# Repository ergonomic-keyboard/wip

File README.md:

# Custom Keyboard Generator

A browser-based tool for designing custom split ergonomic keyboards. Tap your finger positions, preview in 3D, and get a complete bill of materials with purchase links.

## Quick Start

Launch both the keyboard wizard and the requirement tracker:

```bash
cd /home/a/git/git/keyboard/wip
fuser -k 8080/tcp 8099/tcp 2>/dev/null; python3 -m http.server 8080 & node req-tracker.js & wait
```

- Keyboard wizard: http://localhost:8080/wizard.html
- Requirement tracker: http://localhost:8099

## Keyboard Wizard

Open http://localhost:8080/wizard.html and follow the 4 steps:

1. **Tap finger positions** — place your left hand flat and tap 3 key positions per finger column (pinky through thumb)
2. **3D preview** — interactive 3D model with shadows, wooden frame enclosure, click-to-press keys, exploded view, and component labels
3. **Bill of materials** — full parts list with prices and purchase links, download design files as a ZIP
4. **Firmware & test** — generated ZMK shield files, keymap visualization, native_posix hardware emulation tests

## Requirement Tracker

Tracks PASS/FAIL/SKIP status for each requirement in `final_requirements.md`, per git commit.

```bash
node req-tracker.js
```

Open http://localhost:8099.

**Features:**
- Each requirement from `final_requirements.md` is shown with its full text
- Mark each requirement PASS, FAIL, or SKIP
- Click the comment button to add notes (e.g. what's wrong, how to fix it)
- Edit requirement text inline (click the text, edit, click away to save)
- Add new requirements with the "+ Add requirement" button
- Navigate between git commits using the arrows in the top-right
- When navigating to a commit with no status, it inherits PASS/FAIL/SKIP from the nearest reviewed commit (comments are per-commit and not inherited)

**Storage:**
- Status files are saved in `req-status/<commit-hash>.json`
- These files are inside the git repo — commit them to sync progress to GitHub
- Requirement edits are saved directly to `final_requirements.md`

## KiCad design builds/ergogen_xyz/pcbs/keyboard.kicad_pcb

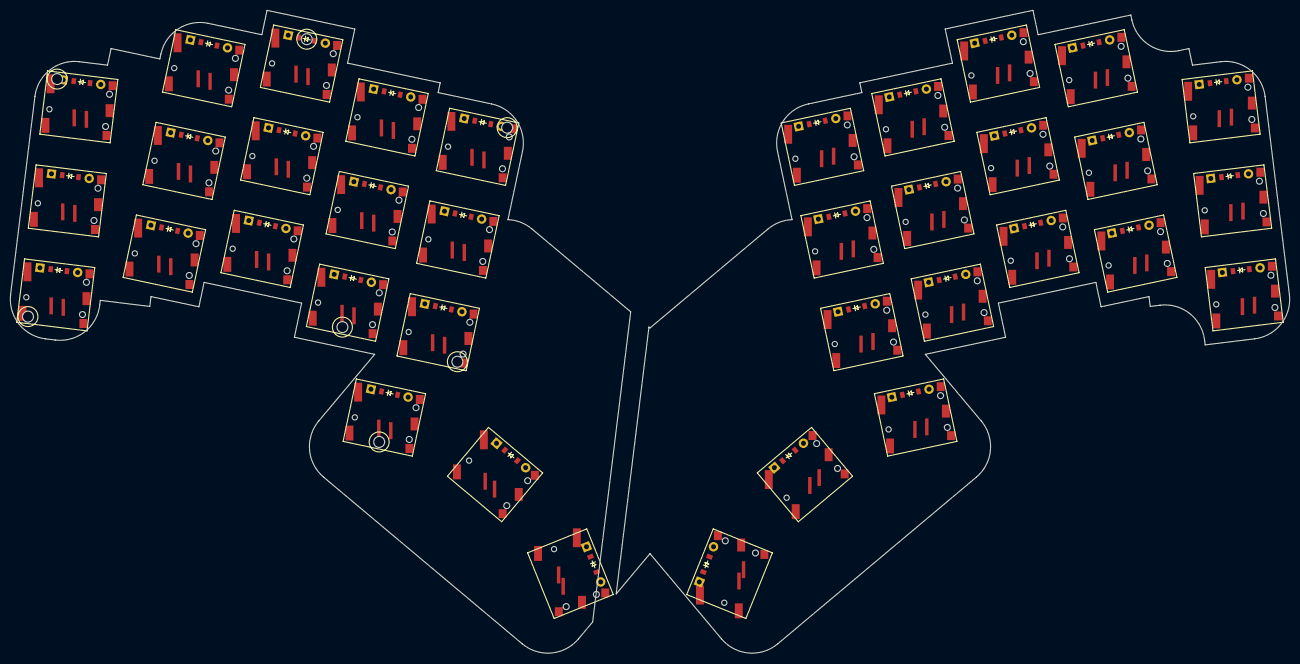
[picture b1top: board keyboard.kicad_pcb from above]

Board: 2 copper layers, 256.6 x 128.9 mm, 79 parts (0 on the bottom side), 36 nets, no tracks yet.

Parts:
D1, D2, D3, D4, D5, D6, D7, D8, D9, D10, D11, D12, D13, D14, D15, D16, D17, D18, D19, D20, D21, D22, D23, D24, D25, D26, D27, D28, D29, D30, D31, D32, D33, D34, D35, D36: ComboDiode
MH1, MH2, MH3, MH4, MH5, MH6, MH7: MountingHole_M2
S1, S2, S3, S4, S5, S6, S7, S8, S9, S10, S11, S12, S13, S14, S15, S16, S17, S18, S19, S20, S21, S22, S23, S24, S25, S26, S27, S28, S29, S30, S31, S32, S33, S34, S35, S36: Cherry_ULP_SMD

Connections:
far_thumb: D18.2, S18.2
home_thumb: D17.2, S17.2
index_bottom: D10.2, S10.2
index_home: D11.2, S11.2
index_top: D12.2, S12.2
inner_bottom: D13.2, S13.2
inner_home: D14.2, S14.2
inner_top: D15.2, S15.2
middle_bottom: D7.2, S7.2
middle_home: D8.2, S8.2
middle_top: D9.2, S9.2
mirror_far_thumb: D36.2, S36.2
mirror_home_thumb: D35.2, S35.2
mirror_index_bottom: D28.2, S28.2
mirror_index_home: D29.2, S29.2
mirror_index_top: D30.2, S30.2
mirror_inner_bottom: D31.2, S31.2
mirror_inner_home: D32.2, S32.2
mirror_inner_top: D33.2, S33.2
mirror_middle_bottom: D25.2, S25.2
mirror_middle_home: D26.2, S26.2
mirror_middle_top: D27.2, S27.2
mirror_near_thumb: D34.2, S34.2
mirror_pinky_bottom: D19.2, S19.2
mirror_pinky_home: D20.2, S20.2
mirror_pinky_top: D21.2, S21.2
mirror_ring_bottom: D22.2, S22.2
mirror_ring_home: D23.2, S23.2
mirror_ring_top: D24.2, S24.2
near_thumb: D16.2, S16.2
pinky_bottom: D1.2, S1.2
pinky_home: D2.2, S2.2
pinky_top: D3.2, S3.2
ring_bottom: D4.2, S4.2
ring_home: D5.2, S5.2
ring_top: D6.2, S6.2

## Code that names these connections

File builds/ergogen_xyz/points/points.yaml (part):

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        autobind: 10
        skip: false
        asym: both
        colrow: pinky_bottom
        name: matrix_pinky_bottom
        zone:
            columns:
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        autobind: 10
        skip: false
        asym: both
        colrow: pinky_home
        name: matrix_pinky_home
        zone:
            columns:
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        autobind: 10
        skip: false
        asym: both
        colrow: pinky_top
        name: matrix_pinky_top
        zone:
            columns:
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        autobind: 10
        skip: false
        asym: both
        colrow: mirror_pinky_bottom
        name: mirror_matrix_pinky_bottom
        zone:
            columns:
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        autobind: 10
        skip: false
        asym: both
        colrow: mirror_pinky_home
        name: mirror_matrix_pinky_home
        zone:
            columns:
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        autobind: 10
        skip: false
        asym: both
        colrow: mirror_pinky_top
        name: mirror_matrix_pinky_top
        zone:
            columns:
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
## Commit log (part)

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2026-05-03 Included initial start.
2026-05-08 Included final requirements.md
2026-05-08 Refined folding requirements.
2026-05-08 Separted folding requirement specification.
2026-05-08 Finalised initial requirements.
2026-05-08 Removed unused data.
2026-05-08 Updated thumb requirements.
2026-05-08 Initial requirements.
2026-05-08 Include verification plan.
2026-05-08 Before rewrite.
2026-05-08 Tried to improve the render.
2026-05-08 Included original key positions.
2026-05-09 Corrected thumb column
2026-05-09 Corrected thumb coordintes.
2026-05-10 Increased trasnaparancy.
2026-05-10 Corrected butterfly fold.
2026-05-10 Moved chips into shell.
2026-05-10 Noticed NiceNano is not at edge and updated scorecard.
2026-05-10 Included requirement on nicenano on back.
2026-05-10 Moved axis and included nano position .
2026-05-10 Moved nicenano.
2026-05-10 Included compliance tracker.
2026-05-10 Included initial requirement judgement.
2026-05-10 Included Requirements Tracker requirements.
2026-05-10 Split requirements into subrequirements.
2026-05-10 Increased requirement review.
2026-05-10 Increased requirements compliance assessment.
2026-05-10 Included CI for website.
2026-05-10 Included defualt render.
2026-05-10 Included component label requirement.
2026-05-10 Removed unused outdated file.
2026-05-10 Gave first try on cables.
2026-05-10 Made hardware components and modelling modular.
2026-05-10 Included more hinges.
2026-05-11 Included hinge poles.
2026-05-11 Tried to remove artifacts that were nuts and bolts.
2026-05-11 Redistributed nuts and bolts.
2026-05-11 Updated requirements.
2026-05-11 6 retries.
2026-05-14 Moved scorecard into requirements website.
2026-05-17 Moved nut positions.
2026-05-17 Corrected nut and bolt positions.
2026-06-01 Initial hinge retry.
2026-06-01 Included switch configuration step.
2026-06-01 Found swapped positions left to right.
2026-06-01 Swapped left right switch labels.
2026-06-07 Updated requirement compliance.
2026-06-07 Corrected thumb switch label positions.
2026-06-07 Included handover.
2026-06-14 Included fold requirements.
